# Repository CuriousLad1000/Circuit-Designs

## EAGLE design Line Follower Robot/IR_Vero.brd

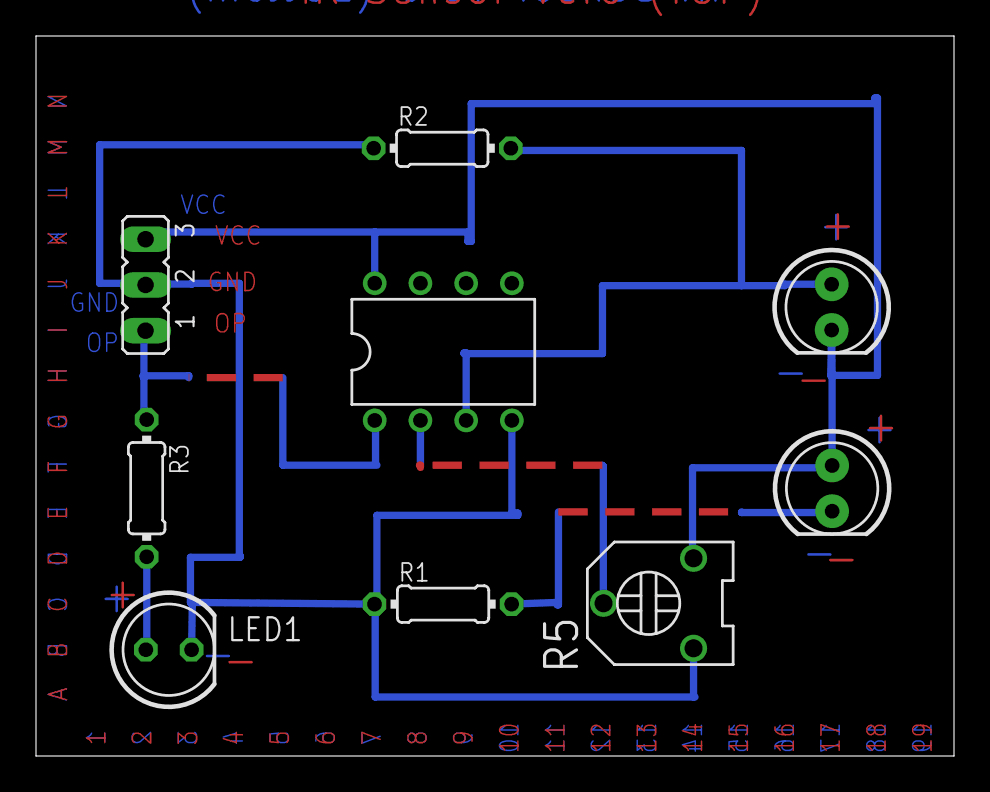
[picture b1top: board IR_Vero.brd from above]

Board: 2 copper layers, 51.0 x 40.0 mm, 28 parts (0 on the bottom side), 5 nets.

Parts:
1, 2, 4: 1X14
D1: IR TX; LED_5MM
D2: IR RX; LED_5MM
IC1: LM358N; DIL08
JP1: JP2
JP3, JP5, JP6, JP7, JP8, JP9, JP10, JP11, JP12, JP13, JP14, JP15, JP16, JP17, JP18, JP19: 1X14
LED1: LED5MM
R1, R3: 330; 0204/7
R2: 10K; 0204/7
R5: 10k; TRIMMER_3306F

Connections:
unnamed: D1.A, D2.K, IC1.8, JP1.3, R5.3
unnamed: D1.K, R1.2
unnamed: IC1.4, JP1.2, LED1.K, R1.1, R2.1, R5.1
unnamed: IC1.2, R5.2
unnamed: D2.A, IC1.3, R2.2

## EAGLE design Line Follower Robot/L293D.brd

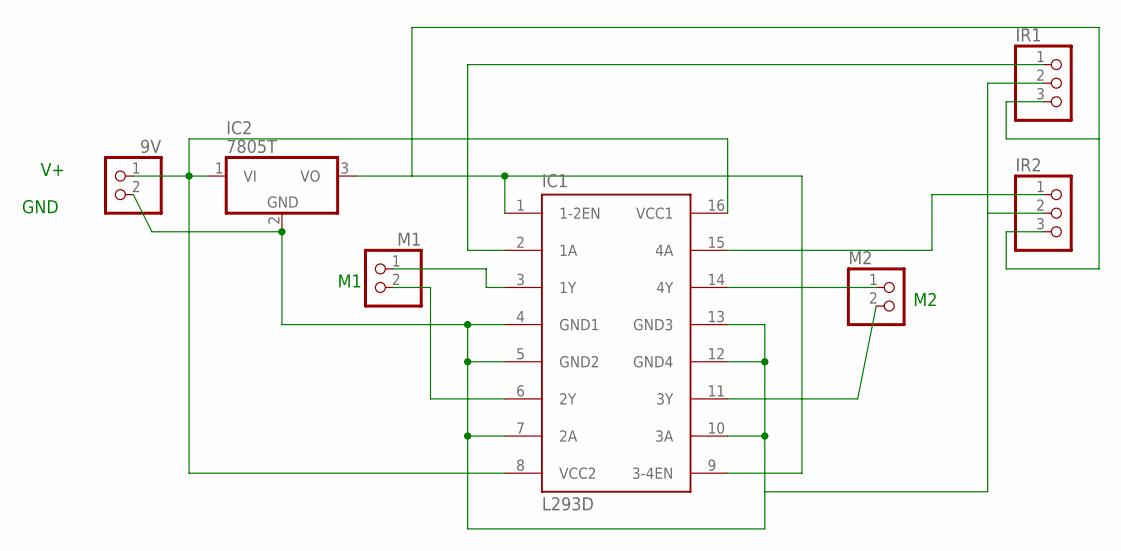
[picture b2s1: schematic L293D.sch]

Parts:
9V: PINHD-1X2; 1X02
IC1: L293D; DIL16
IC2: 7805T; TO220H
IR1, IR2: PINHD-1X3; 1X03
M1, M2: PINHD-1X2; 1X02

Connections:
unnamed: IC1.1 (1-2EN), IC1.9 (3-4EN), IC2.3 (VO), IR1.3, IR2.3
unnamed: 9V.2, IC1.4 (GND1), IC1.5 (GND2), IC1.7 (2A), IC1.10 (3A), IC1.12 (GND4), IC1.13 (GND3), IC2.2 (GND), IR1.2, IR2.2
unnamed: IC1.6 (2Y), M1.2
unnamed: IC1.14 (4Y), M2.1
unnamed: IC1.3 (1Y), M1.1
unnamed: IC1.11 (3Y), M2.2
unnamed: IC1.2 (1A), IR1.1
unnamed: IC1.15 (4A), IR2.1
unnamed: 9V.1, IC1.8 (VCC2), IC1.16 (VCC1), IC2.1 (VI)

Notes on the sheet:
GND

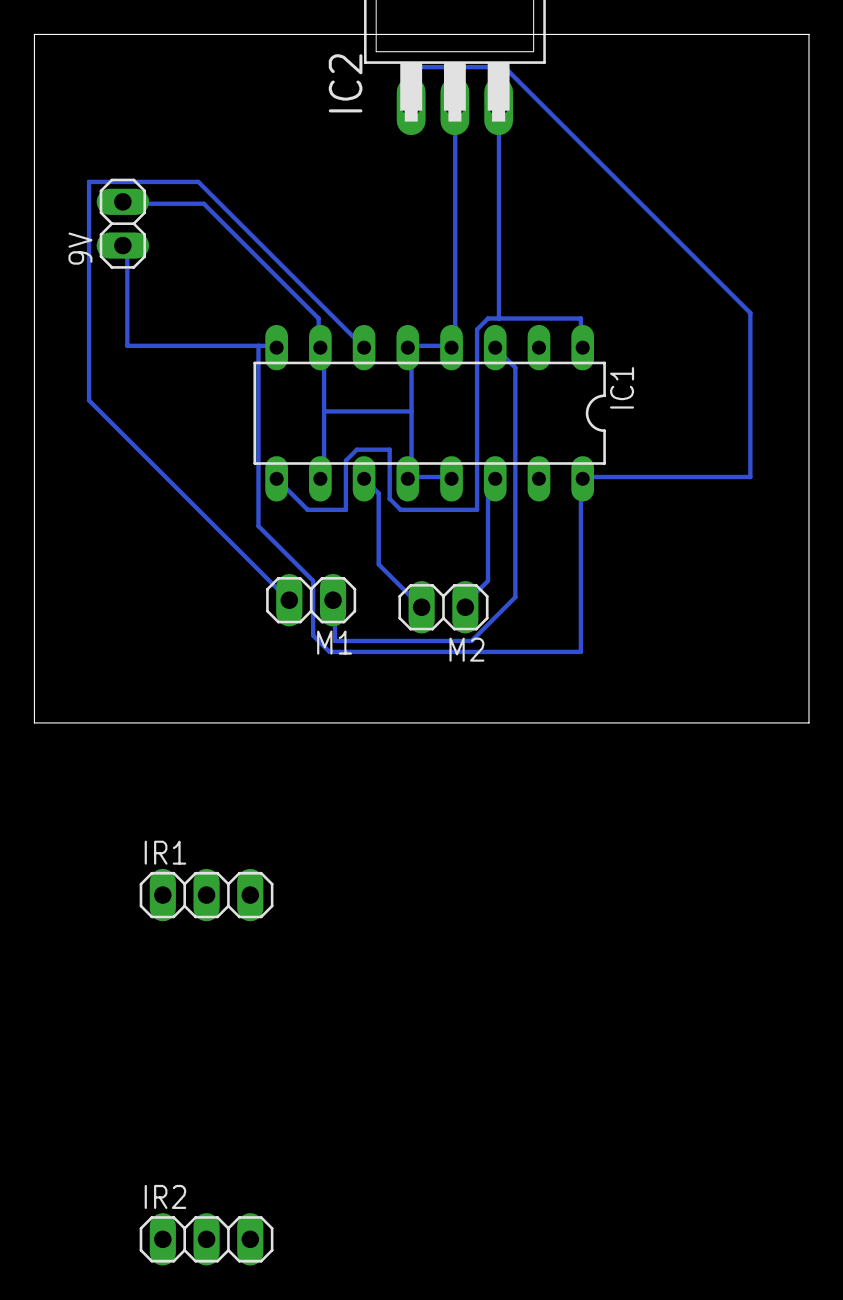
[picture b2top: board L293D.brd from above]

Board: 2 copper layers, 45.0 x 40.0 mm, 7 parts (0 on the bottom side), 9 nets.

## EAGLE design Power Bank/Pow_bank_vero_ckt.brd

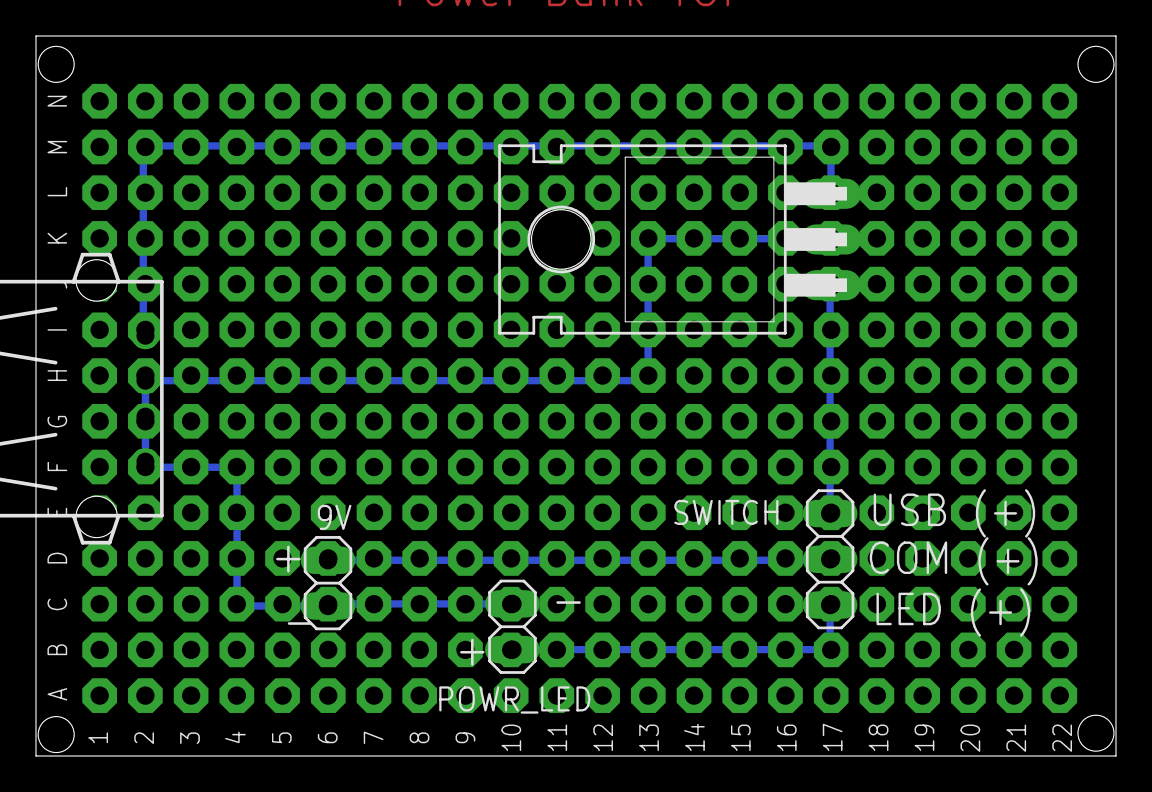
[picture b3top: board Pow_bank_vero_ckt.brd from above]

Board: 2 copper layers, 60.0 x 40.0 mm, 27 parts (0 on the bottom side), 5 nets.

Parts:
1, 2, 4: 1X14
9V: 1X02
IC1: 7805T; TO220H
JP3, JP5, JP6, JP7, JP8, JP9, JP10, JP11, JP12, JP13, JP14, JP15, JP16, JP17, JP18, JP19, JP20, JP21, JP22: 1X14
POWR_LED: 1X02
SWITCH: 1X03
X1: USB

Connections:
GND: 9V.2, IC1.2, POWR_LED.2, X1.2, X1.3, X1.4
unnamed: IC1.1, SWITCH.1
unnamed: IC1.3, X1.1
unnamed: POWR_LED.1, SWITCH.3
VCC: 9V.1, SWITCH.2

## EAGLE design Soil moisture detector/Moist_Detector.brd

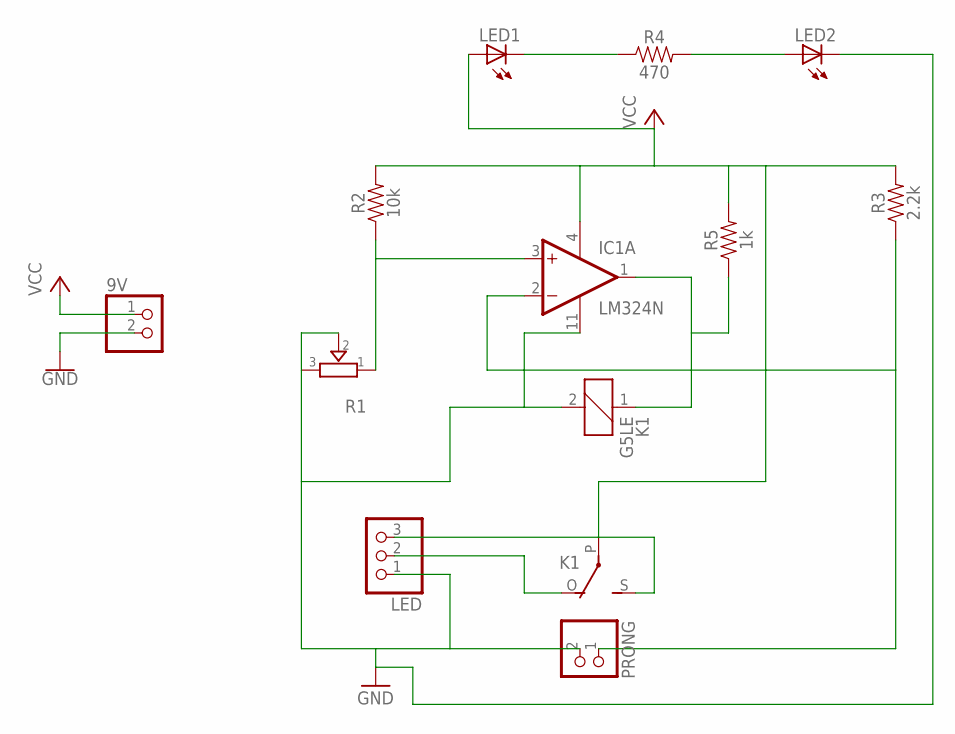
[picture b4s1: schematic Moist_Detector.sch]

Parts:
9V: PINHD-1X2; 1X02
IC1: LM324N; DIL14
K1: G5LE
LED: PINHD-1X3; 1X03
LED1, LED2: LED-5MM
PRONG: PINHD-1X2; 1X02
R1: TRIMMER-3306F; TRIMMER_3306F
R2: 10k; AXIAL-0.3
R3: 2.2k; AXIAL-0.3
R4: 470; AXIAL-0.3
R5: 1k; AXIAL-0.3

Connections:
GND: 9V.2, IC1.11 (V-), K1.2, LED.1, LED2.K (C), PRONG.2, R1.2, R1.3
unnamed: K1.O, LED.2
unnamed: IC1.3 (+IN), R1.1, R2.P$1 (1)
unnamed: K1.S, LED.3
unnamed: IC1.2 (-IN), PRONG.1, R3.P$1 (1)
unnamed: IC1.1 (OUT), K1.1, R5.P$1 (1)
unnamed: LED1.K (C), R4.P$1 (1)
unnamed: LED2.A, R4.P$2 (2)
VCC: 9V.1, IC1.4 (V+), K1.P, LED1.A, R2.P$2 (2), R3.P$2 (2), R5.P$2 (2)

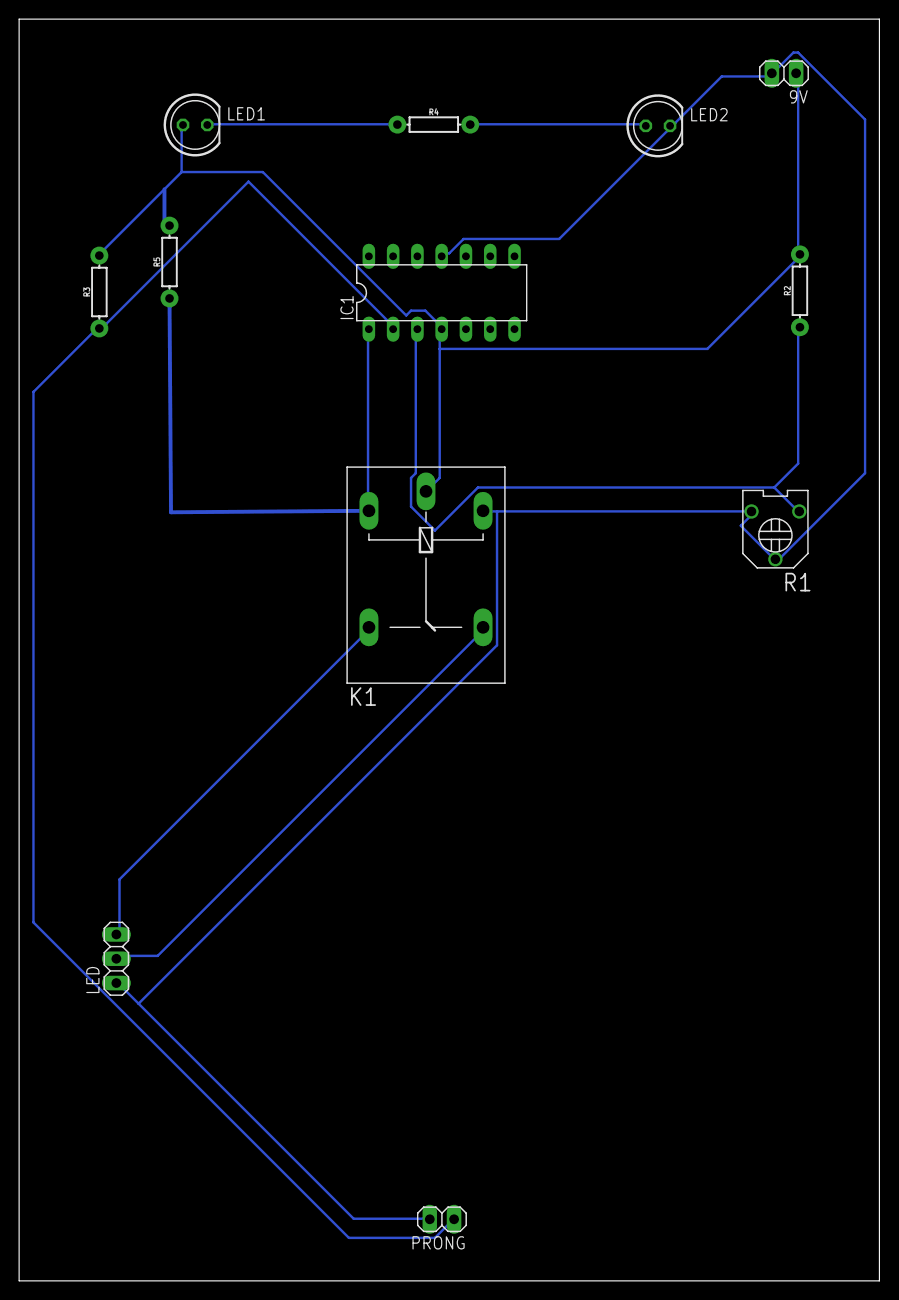
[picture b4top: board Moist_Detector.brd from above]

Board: 2 copper layers, 90.0 x 132.0 mm, 12 parts (0 on the bottom side), 9 nets.

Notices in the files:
parts and their libraries:
SparkFun-LED: Licensing: Creative Commons ShareAlike 4.0 International - https://creativecommons.org/licenses/by-sa/4.0
